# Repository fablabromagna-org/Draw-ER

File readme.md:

# Draw-ER
### da un'idea originale di [MakersBox](https://www.instructables.com/Arduino-Drawing-Robot/)
Un piccolo, lento ma economico robot disegnatore, autocostruibile da tutti e programmabile in Python per insegnare il coding in modo divertente.

# Eccolo

## stampa la locandina da tenere in classe

## istruzioni per il montaggio

<a href="https://cutt.ly/montaggio-Draw-ER">link al documento GDocs</a>

#### Ci serve un fornitore per queste viti... ci date una mano?

#### questa foto è utile per capire come sono montati i connettori

## usa Kicad per modificare lo schema e il PCB

<a href="https://github.com/fablabromagna-org/Draw-ER/tree/master/File%20Kicad">Kicad</a>

## dai un'occhiata allo schema
<a href="Schematic.pdf">Download PDF</a>

## dai un'occhiata anche al lavoro di Alessandro Capanna Kappa! che sta cercando in tutti i modi di togliere il filo!! :-)
https://github.com/1Kappa1/Draw-Er.utility.file

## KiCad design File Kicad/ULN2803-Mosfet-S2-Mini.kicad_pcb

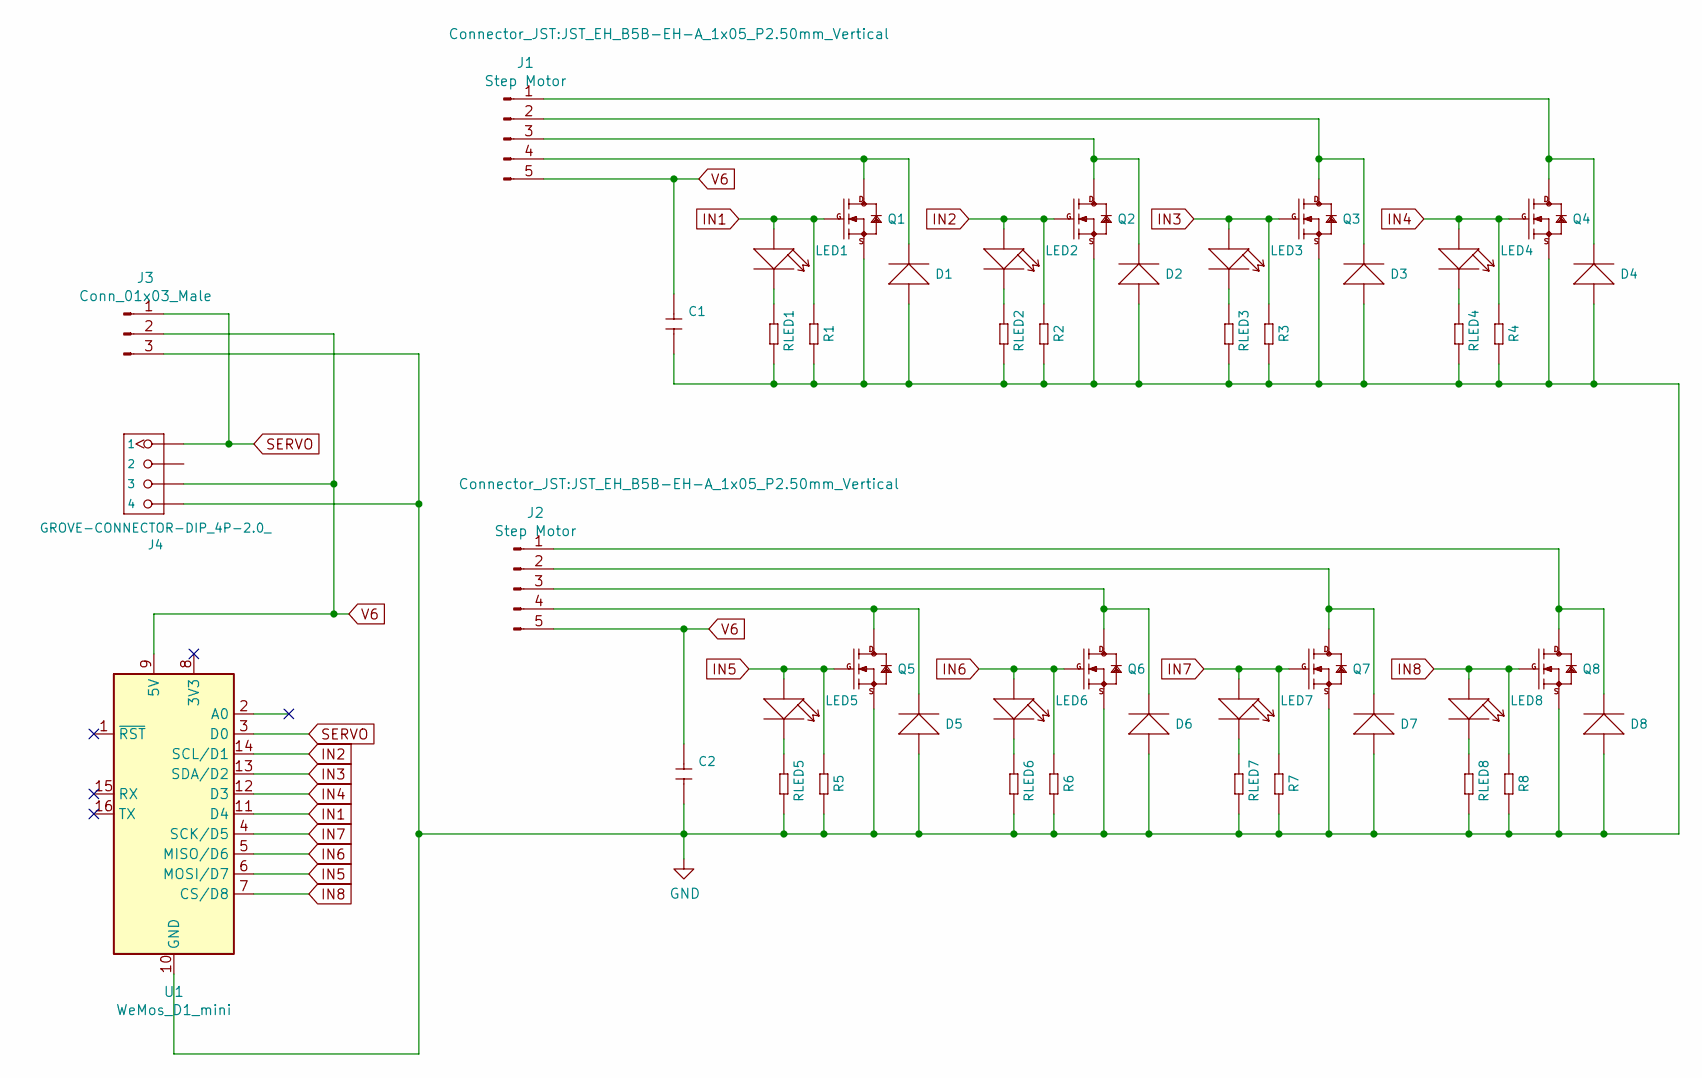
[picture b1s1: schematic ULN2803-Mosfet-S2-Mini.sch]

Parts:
C1, C2: CERAMIC-10UF-10V-10%-X7R_0805_; C0805; MPN CC0805ZKY5V6BB106; LCSC C126586
D1, D2, D3, D4, D5, D6, D7, D8: SMD-DIODE-SCHOTTKY-20V-1A_SOD-123_; SOD-123; MPN B5819W; LCSC C84354
J1, J2: Step Motor; JST_EH_B5B-EH-A_1x05_P2.50mm_Vertical
J3: Conn_01x03_Male; PinHeader_1x03_P2.54mm_Vertical
J4: GROVE-CONNECTOR-DIP_4P-2.0_; HW4-2.0
LED1, LED2, LED3, LED4, LED5, LED6, LED7, LED8: SMD-LED-CLEAR-RED_0805_; LED-0805; MPN 17-215SURC_S530-A2_TR8; LCSC C2764885
Q1, Q2, Q3, Q4, Q5, Q6, Q7, Q8: SMD-MOSFET-N-CH-20V-2.1A-CJ2302_SOT-23_; SOT-23; MPN CJ2302; LCSC C91104
R1, R2, R3, R4, R5, R6, R7, R8: SMD-RES-4.7K-5%-1_8W_0805_; R0805; MPN RC0805JR-074K7L; LCSC C473295
RLED1, RLED2, RLED3, RLED4, RLED5, RLED6, RLED7, RLED8: SMD-RES-220R-5%-1_8W_0805_; R0805; MPN RC0805JR-07220RL; LCSC C365277
U1: WeMos_D1_mini; WEMOS_D1_mini_light

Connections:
GND: C1.2, C2.2, D1.1 (+), D2.1 (+), D3.1 (+), D4.1 (+), D5.1 (+), D6.1 (+), D7.1 (+), D8.1 (+), J3.3, J4.4, Q1.2 (S), Q2.2 (S), Q3.2 (S), Q4.2 (S), Q5.2 (S), Q6.2 (S), Q7.2 (S), Q8.2 (S), R1.2, R2.2, R3.2, R4.2, R5.2, R6.2, R7.2, R8.2, RLED1.2, RLED2.2, RLED3.2, RLED4.2, RLED5.2, RLED6.2, RLED7.2, RLED8.2, U1.10 (GND)
IN1: LED1.1 (+), Q1.1 (G), R1.1, U1.11 (D4)
IN2: LED2.1 (+), Q2.1 (G), R2.1, U1.14 (SCL/D1)
IN3: LED3.1 (+), Q3.1 (G), R3.1, U1.13 (SDA/D2)
IN4: LED4.1 (+), Q4.1 (G), R4.1, U1.12 (D3)
IN5: LED5.1 (+), Q5.1 (G), R5.1, U1.6 (MOSI/D7)
IN6: LED6.1 (+), Q6.1 (G), R6.1, U1.5 (MISO/D6)
IN7: LED7.1 (+), Q7.1 (G), R7.1, U1.4 (SCK/D5)
IN8: LED8.1 (+), Q8.1 (G), R8.1, U1.7 (CS/D8)
unnamed: D1.2 (-), J1.4, Q1.3 (D)
unnamed: D2.2 (-), J1.3, Q2.3 (D)
unnamed: D3.2 (-), J1.2, Q3.3 (D)
unnamed: D4.2 (-), J1.1, Q4.3 (D)
unnamed: D5.2 (-), J2.4, Q5.3 (D)
unnamed: D6.2 (-), J2.3, Q6.3 (D)
unnamed: D7.2 (-), J2.2, Q7.3 (D)
unnamed: D8.2 (-), J2.1, Q8.3 (D)
unnamed: LED1.2 (-), RLED1.1
unnamed: LED2.2 (-), RLED2.1
unnamed: LED3.2 (-), RLED3.1
unnamed: LED4.2 (-), RLED4.1
unnamed: LED5.2 (-), RLED5.1
unnamed: LED6.2 (-), RLED6.1
unnamed: LED7.2 (-), RLED7.1
unnamed: LED8.2 (-), RLED8.1
SERVO: J3.1, J4.1, U1.3 (D0)
V6: C1.1, C2.1, J1.5, J2.5, J3.2, J4.3, U1.9 (5V)

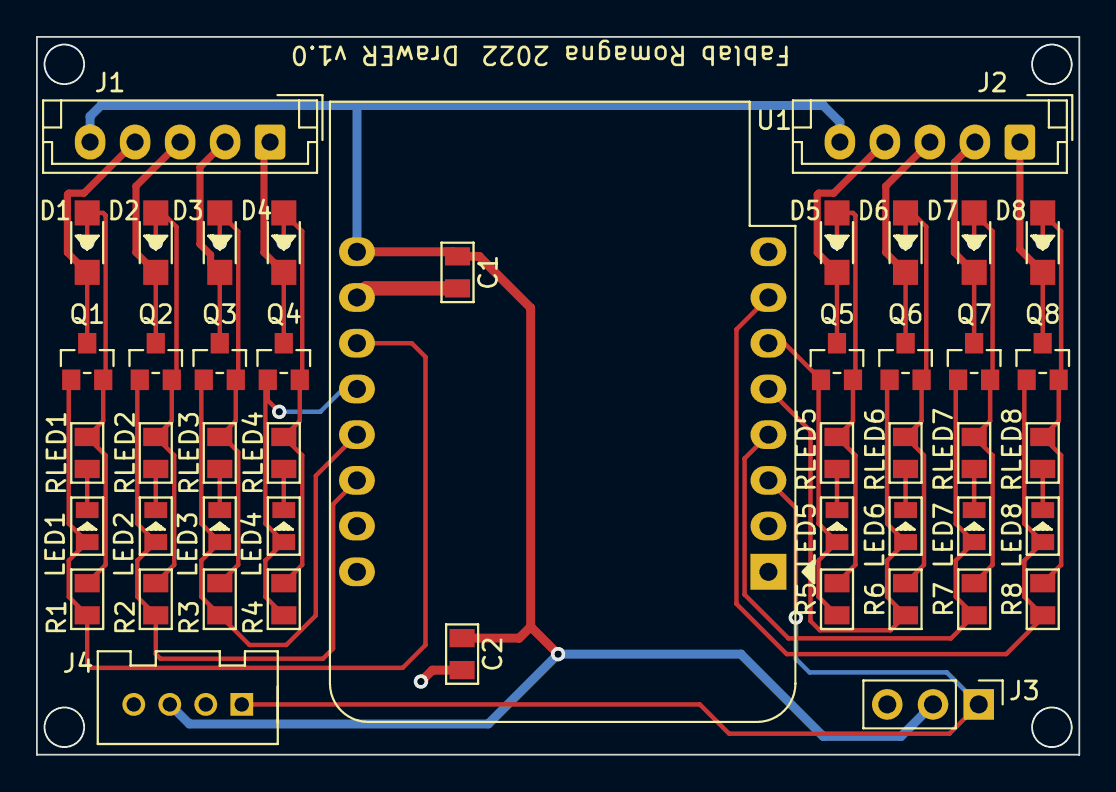
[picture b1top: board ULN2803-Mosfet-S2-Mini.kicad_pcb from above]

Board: 2 copper layers, 57.9 x 39.9 mm, 47 parts (0 on the bottom side), 27 nets.

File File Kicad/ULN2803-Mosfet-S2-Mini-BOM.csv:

Comment,Designator,Footprint,LCSC
"CERAMIC-10UF-10V-10%-X7R_0805_","C1,C2","OPL_Capacitor:C0805","C126586"
"SMD-DIODE-SCHOTTKY-20V-1A_SOD-123_","D1,D2,D3,D4,D5,D6,D7,D8","OPL_Discrete:SOD-123","C84354"
"Step Motor","J1,J2","Connector_JST:JST_EH_B5B-EH-A_1x05_P2.50mm_Vertical",""
"Conn_01x03_Male","J3","Connector_PinHeader_2.54mm:PinHeader_1x03_P2.54mm_Vertical",""
"GROVE-CONNECTOR-DIP_4P-2.0_","J4","OPL_Connector:HW4-2.0",""
"SMD-LED-CLEAR-RED_0805_","LED1,LED2,LED3,LED4,LED5,LED6,LED7,LED8","OPL_Opto:LED-0805","C2764885"
"SMD-MOSFET-N-CH-20V-2.1A-CJ2302_SOT-23_","Q1,Q2,Q3,Q4,Q5,Q6,Q7,Q8","OPL_Discrete:SOT-23","C91104"
"SMD-RES-4.7K-5%-1_8W_0805_","R1,R2,R3,R4,R5,R6,R7,R8","OPL_Resistor:R0805","C473295"
"SMD-RES-220R-5%-1_8W_0805_","RLED1,RLED2,RLED3,RLED4,RLED5,RLED6,RLED7,RLED8","OPL_Resistor:R0805","C365277"
"WeMos_D1_mini","U1","Module:WEMOS_D1_mini_light",""

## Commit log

2022-05-22 Primo commit
2022-05-25 25 maggio
2022-05-28 28 maggio
2022-12-15 Link al lavoro di 1kappa1 su BLE
